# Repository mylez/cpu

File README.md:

#### Miles Smith

# 16-Bit Multiprogram Computer
- Supports kernel and user modes.
- Supports interrupts and exceptions for segmentation violations, timeouts, IO etc (via kernel routine).
- Supports user memory protection through virtual pages (64KB data / 128KB code address space per process).
- Supports preemptive multiprogramming via a hardware timer.

## Instruction Set Architecture (ISA)
##### Total: 57 instructions (57 of 128 opcodes reserved)

### Arithmetic Instructions
##### (16)
    add  rx ry rz           (rx <- ry + rz, status updated)
    sub  rx ry rz           (rx <- ry + rz, status updated)
    and  rx ry rz           (rx <- ry & rz, status updated)
    or   rx ry rz           (rx <- ry | rz, status updated)
    xor  rx ry rz           (rx <- ry ^ rz, status updated)
    sgx  rx ry              (rx <- sigex(ry), status updated)
    shl  rx ry              (rx <- shiftl(ry), status updated)
    shr  rx ry              (rx <- shiftr(ry), status updated)
                (imm values)
    add  rx im rz           (rx <- ry + rz, status updated)
    sub  rx im rz           (rx <- ry + rz, status updated)
    and  rx im rz           (rx <- ry & rz, status updated)
    or   rx im rz           (rx <- ry | rz, status updated)
    xor  rx im rz           (rx <- ry ^ rz, status updated)
    sgx  rx im              (rx <- sigex(ry), status updated)
    shl  rx im              (rx <- shiftl(ry), status updated)
    shr  rx im              (rx <- shiftr(ry), status updated)
     ...  (will vary based on alu implementation) ...

### MMIO Instructions
##### (15)
    l    rx ry rz           (vmem_data[ry + rz] <- rx) *
    li   imm                (r7 <- imm) *
    s    rx ry rz           (rx <- vmem_data[...]) *
    lb   rx ry rz           (vmem_data[...] <- rx, byte) *
    sb   rx ry rz           (rx <- vmem_data[...], byte) *
    ats  rx ry rz           (atomic test and set, vmem, byte) *
    lc   rx ry rz           (rx <- vmem_code[...])
    sc   rx ry rz           (vmem_code[...] <- rx)
    kl   rx ry rz           (kmem_data[...] <- rx)
    ks   rx ry rz           (rx <- kmem_data[...], byte)
    kats rx ry rz           (atomic test and set, kernel mem, byte)
    klb  rx ry rz           (rx <- kmem_data[...], byte)
    ksb  rx ry rz           (kmem_data[...] <- rx)
    klc  rx ry rz           (rx <- kmem_code[...])
    ksc  rx ry rz           (kmem_code[...] <- rx)
    
    * l, s, lb, sb, li, and ats are the only mmio instructions available to user programs
    (ie unprotected). all other MMIO instructions are protected instructions.

### Control Flow Instructions
##### (14)
    beq ry rz               branch if equal (pc <- $ry + rz)
    bne ry rz               branch if not equal
    bng ry rz               branch if negative
    bov ry rz               branch if overflow
    bcy ry rz               branch if carry
    b   ry rz               branch (unconditional)
              (imm values)
    beq im rz               branch if equal (r7 <- im, pc <- im + rz)
    bne im rz               branch if not equal
    bng im rz               branch if negative
    bov im rz               branch if overflow
    bcy im rz               branch if carry
    b   im rz
    cll im                  function call (r7 <- pc, pc <- imm, return via add, l, li, ...etc)
    sys im                  system call via exception (r7 <- return value)
      ... (will vary based on implementation) ...

### Kernel / Special Instructions
##### (12)
    ktime   rx              kernel load timer: timer <- rx
    kuser                   enable user mode
    kcaus   rx              kernel read cause: rx <- cause
    keret   rx              kernel read exception return addr: rx <- eret
    kaddr   rx              kernel read exception virtual address: rx <- exc_addr
    kcont   rx              kernel read context register: rx <- context
    krout   rx              kernel read isr register: rx <- isr
    kbase   rx              load page table base register: ptb <- rx
    kptes   rx ry rz        store page table entry, ptb[ry + rz] <- rx
    kptel   rx ry rz        load page table entry, rx <- ptb[ry + rz]
    statr   rx              read status register: rx <- status **
    statl   rx              load status register: status <- rx **

    ** statr and statl are unprotected. all others on the kernel / special list
    are protected instructions.

## Register Layout
### User Registers
There are 8 registers available to a user program. These are:

    r0 - A constant, hard-wired value of zero.
    r1 - General purpose register 1.
    r2 - General purpose register 2.
    r3 - General purpose register 3.
    r4 - Base pointer.
    r5 - Stack pointer.
    r6 - Program counter.
    r7 - Special register (imm. value / int. return value / return address)

### Kernel / Special Registers
There are 7 registers dedicated to kernel functions and special applications. These are:

    status -  Contains the result of the last ALU operation as NZVF used for conditional 
              branching. User-accessible.
    timer -   Preemption timer. Decremented while in user mode. Once it reaches zero,
              it signals a preemption exception. Protected.
    cause -   Contains information about which interrupt or exception the kernel is 
              servicing. Protected.
    eaddr -   Contains the bad virtual address that triggerred an exception, if 
              applicable. Protected.
    eret -    Contains the value of the PC when the exception/interrupt occurred. Used 
              in context switching. Protected.
    context - Contains the value of the r7 when the exception/interrupt occurred. Used 
              in context switching. Protected.
    isr -     Contains the hardwired address of the global kernel interrupt service routine.
    
### Memory Segmentation

Memory is split across both user/kernel domains as well as data/code domains. The
kernel segments are always addressed using physical addresses, while the user segments
are always addressed using virtual address translation via the MMU. In kernel mode,
the CPU will execute code from the kernel code segment. In user mode, it will execute
from the data segment.

In addition to virtual pages for user processes, processes running in kernel mode may
access the kernel RAM / ROM using physical addresses - ie there is only one kernel
address space. The CPU will begin to execute from this kernel address space on startup,
or when handling an exception.

A benefit of this approach is that it allows for data and code to occupy separate
address spaces. Data is byte-addressed. Code is 16 bit word-addressed (since all
instructions are alligned 2-byte boundaries). This provides a larger code memory (192KB in total).

A drawback of this approach is that kernel processes can not share memory with
user processes, and extra care is required in kernel mode to use the appropriate 
instruction the segment you wish to read to or write from.

## Logisim Schematics
#### CPU Main Circuit

#### MMIO Module

#### MMU Module

#### Control Module

#### Control State Diagram

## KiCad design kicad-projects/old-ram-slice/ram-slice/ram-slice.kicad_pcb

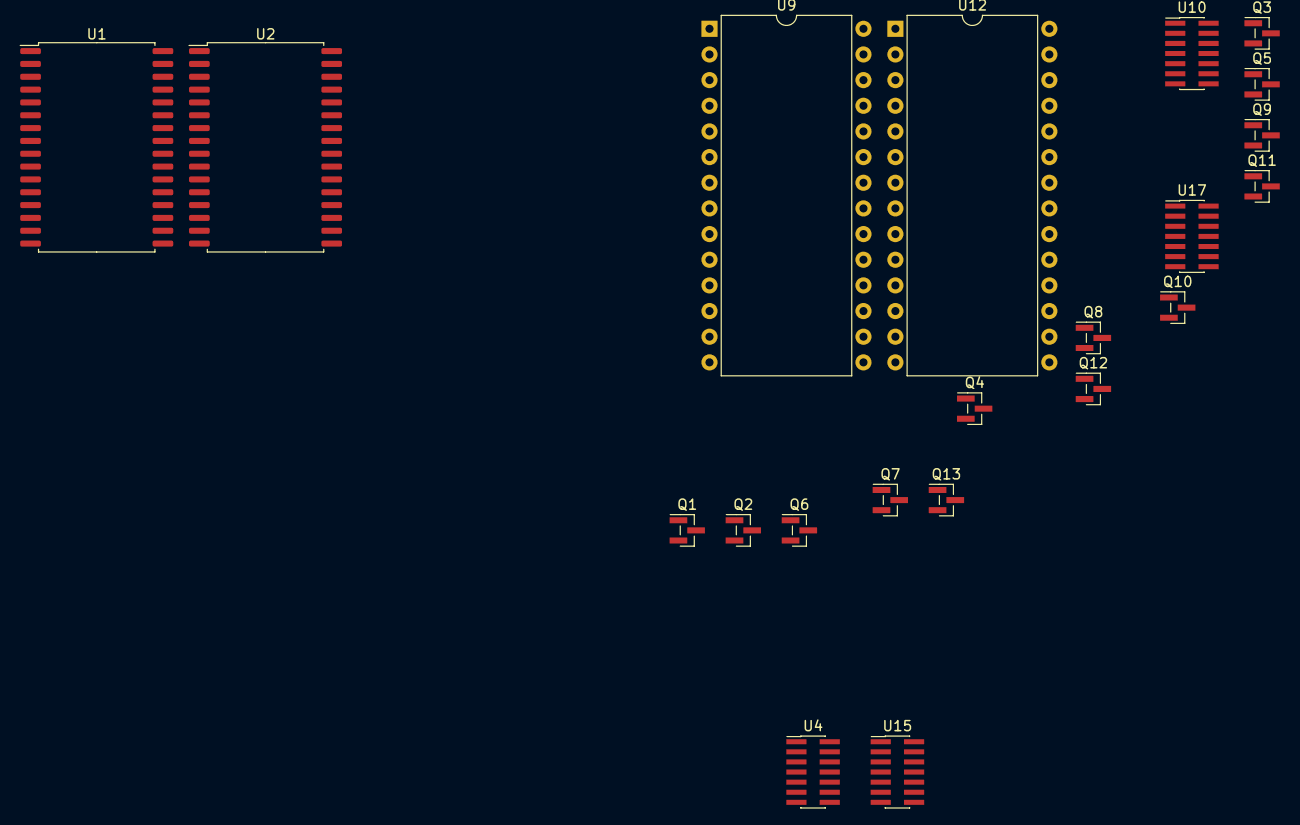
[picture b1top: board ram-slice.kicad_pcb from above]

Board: 2 copper layers, 21 parts (0 on the bottom side), 42 nets, no tracks yet.

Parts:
Q1, Q2, Q3, Q4, Q5, Q6, Q7, Q8, Q9, Q10, Q11, Q12, Q13: BS170; PinHeader_1x03_P1.00mm_Vertical_SMD_Pin1Left
U1, U2: IS61C5128AS-25QLI; SSOP-32_11.305x20.495mm_P1.27mm
U4, U10: 74LS08; PinHeader_2x07_P1.00mm_Vertical_SMD
U9, U12: 27C64; DIP-28_W15.24mm
U15: 74LS02; PinHeader_2x07_P1.00mm_Vertical_SMD
U17: 74LS32; PinHeader_2x07_P1.00mm_Vertical_SMD

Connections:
/A1: U1.12, U2.12, U9.10, U12.10
/A2: U1.11, U2.11, U9.9, U12.9
/A3: U1.10, U2.10, U9.8, U12.8
/A4: U1.9, U2.9, U9.7, U12.7
/A5: U1.8, U2.8, U9.6, U12.6
/A6: U1.7, U2.7, U9.5, U12.5
/A7: U1.6, U2.6, U9.4, U12.4
/A8: U1.5, U2.5, U9.3, U12.3
/A9: U1.27, U2.27, U9.25, U12.25
/A10: U1.26, U2.26, U9.24, U12.24
/A11: U1.23, U2.23, U9.21, U12.21
/A12: U1.25, U2.25, U9.23, U12.23
/A13: U1.4, U2.4, U9.2, U12.2
/A14: U1.28, U2.28
/A15: U1.3, U2.3
/A16: U1.31, U2.31
/A17: U1.2, U2.2
/A18: U1.1, U2.1
/A19: U1.30, U2.30
/BYTE: U4.2, U10.2
/HIGH0: U2.13, U12.11
/HIGH1: U2.14, U12.12
/HIGH2: U2.15, U12.13
/HIGH3: U2.17, U12.15
/HIGH4: U2.18, U12.16
/HIGH5: U2.19, U12.17
/HIGH6: U2.20, U12.18
/HIGH7: U2.21, U12.19
/HIGH_BYTE: U4.3, U17.4
/LOW0: U1.13, U9.11
/LOW1: U1.14, U9.12
/LOW2: U1.15, U9.13
/LOW3: U1.17, U9.15
/LOW4: U1.18, U9.16
/LOW5: U1.19, U9.17
/LOW6: U1.20, U9.18
/LOW7: U1.21, U9.19
/LOW_BYTE: U10.3, U17.1
/LOW_BYTE_ACCESSED: U17.3, U17.6
/STORE: U10.4, U10.9
/~BYTE: U17.2, U17.5
/~CLK: U10.5, U10.10

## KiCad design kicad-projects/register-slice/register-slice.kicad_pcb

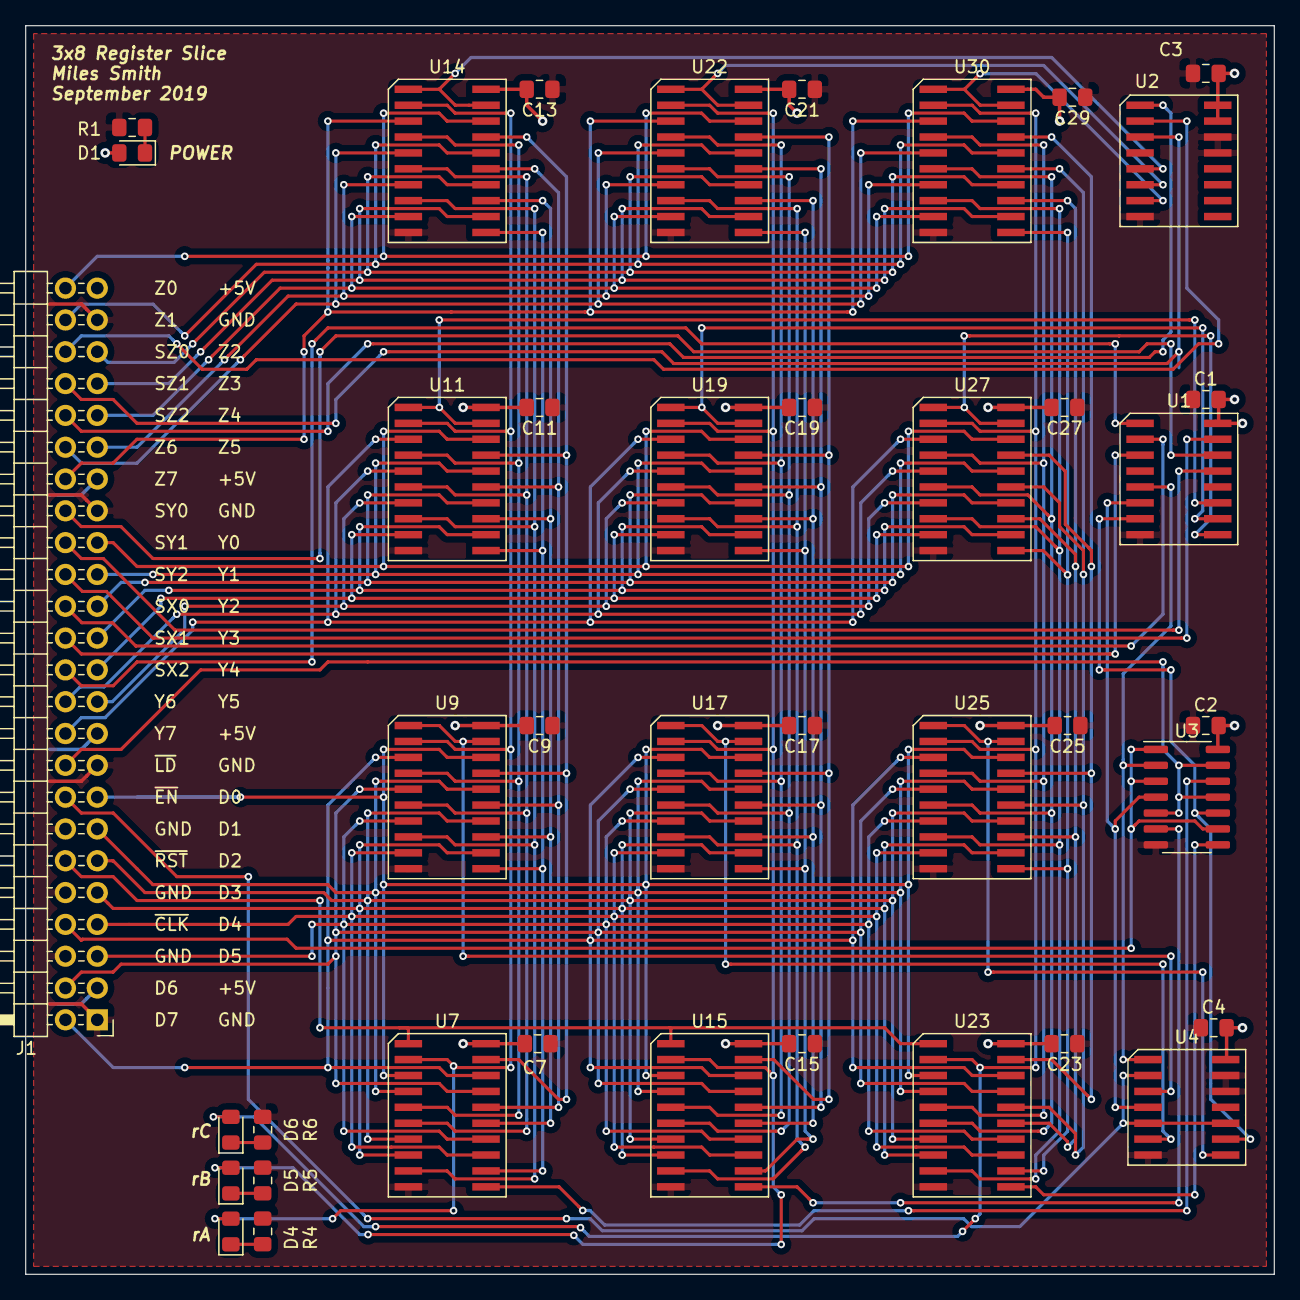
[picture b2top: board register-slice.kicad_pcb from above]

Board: 2 copper layers, 99.7 x 99.7 mm, 41 parts (0 on the bottom side), 82 nets.

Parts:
C1, C2, C3, C4, C7, C9, C11, C13, C15, C17, C19, C21, C23, C25, C27, C29: 0.1 uF; C_0805_2012Metric_Pad1.15x1.40mm_HandSolder
D1: GREEN; LED_0805_2012Metric_Pad1.15x1.40mm_HandSolder
D4, D5, D6: RED; LED_0805_2012Metric_Pad1.15x1.40mm_HandSolder
J1: Conn_02x24_Odd_Even; PinHeader_2x24_P2.54mm_Horizontal
R1, R4, R5, R6: 430; R_0805_2012Metric_Pad1.15x1.40mm_HandSolder
U1, U2: 74LS139; SOIC-16-6.2mm
U3: 74LS27; SOIC-14_3.9x8.7mm_P1.27mm
U4: 74LS32; SOIC-14-6.2mm
U7, U15, U23: 74LS273; SOIC-20-6.2mm
U9, U11, U14, U17, U19, U22, U25, U27, U30: 74LS244; SOIC-20-6.2mm

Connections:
+5V: C1.2, C2.2, C3.2, C4.2, C7.2, C9.2, C11.2, C13.2, C15.2, C17.2, C19.2, C21.2, C23.2, C25.2, C27.2, C29.2, D1.2, J1.3, J1.19, J1.35, J1.47, U1.16, U2.15, U2.16, U3.14, U4.14, U7.20, U9.20, U11.20, U14.20, U15.20, U17.20, U19.20, U22.20, U23.20, U25.20, U27.20, U30.20
/R0A: D4.2, U7.2, U9.2, U11.2, U14.2
/R0B: D5.2, U15.2, U17.2, U19.2, U22.2
/R0C: D6.2, U23.2, U25.2, U27.2, U30.2
/register_a/CP: U3.12, U7.11
/register_a/R1: U7.5, U9.4, U11.4, U14.4
/register_a/R2: U7.6, U9.6, U11.6, U14.6
/register_a/R3: U7.9, U9.8, U11.8, U14.8
/register_a/R4: U7.12, U9.11, U11.11, U14.11
/register_a/R5: U7.15, U9.13, U11.13, U14.13
/register_a/R6: U7.16, U9.15, U11.15, U14.15
/register_a/R7: U7.19, U9.17, U11.17, U14.17
/register_a/~EN_X: U4.3, U9.1, U9.19
/register_b/CP: U3.6, U15.11
/register_b/R1: U15.5, U17.4, U19.4, U22.4
/register_b/R2: U15.6, U17.6, U19.6, U22.6
/register_b/R3: U15.9, U17.8, U19.8, U22.8
/register_b/R4: U15.12, U17.11, U19.11, U22.11
/register_b/R5: U15.15, U17.13, U19.13, U22.13
/register_b/R6: U15.16, U17.15, U19.15, U22.15
/register_b/R7: U15.19, U17.17, U19.17, U22.17
/register_b/~EN_X: U4.6, U17.1, U17.19
/register_c/CP: U3.8, U23.11
/register_c/R1: U23.5, U25.4, U27.4, U30.4
/register_c/R2: U23.6, U25.6, U27.6, U30.6
/register_c/R3: U23.9, U25.8, U27.8, U30.8
/register_c/R4: U23.12, U25.11, U27.11, U30.11
/register_c/R5: U23.15, U25.13, U27.13, U30.13
/register_c/R6: U23.16, U25.15, U27.15, U30.15
/register_c/R7: U23.19, U25.17, U27.17, U30.17
/register_c/~EN_X: U4.8, U25.1, U25.19
/~EN_1_X: U1.5, U3.2, U4.1
/~EN_1_Y: U1.11, U11.1, U11.19
/~EN_1_Z: U2.5, U14.1, U14.19
/~EN_2_X: U1.6, U3.4, U4.4
/~EN_2_Y: U1.10, U19.1, U19.19
/~EN_2_Z: U2.6, U22.1, U22.19
/~EN_3_X: U1.7, U3.10, U4.9
/~EN_3_Y: U1.9, U27.1, U27.19
/~EN_3_Z: U2.7, U30.1, U30.19
D0: J1.15, U7.3, U9.18, U15.3, U17.18, U23.3, U25.18
D1: J1.13, U7.4, U9.16, U15.4, U17.16, U23.4, U25.16
D2: J1.11, U7.7, U9.14, U15.7, U17.14, U23.7, U25.14
D3: J1.9, U7.8, U9.12, U15.8, U17.12, U23.8, U25.12
D4: J1.7, U7.13, U9.9, U15.13, U17.9, U23.13, U25.9
D5: J1.5, U7.14, U9.7, U15.14, U17.7, U23.14, U25.7
D6: J1.4, U7.17, U9.5, U15.17, U17.5, U23.17, U25.5
D7: J1.2, U7.18, U9.3, U15.18, U17.3, U23.18, U25.3
GND: C1.1, C2.1, C3.1, C4.1, C7.1, C9.1, C11.1, C13.1, C15.1, C17.1, C19.1, C21.1, C23.1, C25.1, C27.1, C29.1, J1.1, J1.6, J1.10, J1.14, J1.17, J1.33, J1.45, R1.2, R4.2, R5.2, R6.2, U1.8, U2.8, U2.13, U2.14, U3.7, U4.7, U4.12, U4.13, U7.10, U9.10, U11.10, U14.10, U15.10, U17.10, U19.10, U22.10, U23.10, U25.10, U27.10, U30.10
unnamed: D1.1, R1.1
unnamed: D4.1, R4.1
unnamed: D5.1, R5.1
unnamed: D6.1, R6.1
SEL_X_0: J1.28, U1.2
SEL_X_1: J1.26, U1.3
SEL_Y_0: J1.34, U1.14
SEL_Y_1: J1.32, U1.13
SEL_Z_0: J1.44, U2.2
SEL_Z_1: J1.42, U2.3
Y0: J1.31, U11.18, U19.18, U27.18
Y1: J1.29, U11.16, U19.16, U27.16
Y2: J1.27, U11.14, U19.14, U27.14
Y3: J1.25, U11.12, U19.12, U27.12
Y4: J1.23, U11.9, U19.9, U27.9
Y5: J1.21, U11.7, U19.7, U27.7
Y6: J1.22, U11.5, U19.5, U27.5
Y7: J1.20, U11.3, U19.3, U27.3
Z0: J1.48, U14.18, U22.18, U30.18
Z1: J1.46, U14.16, U22.16, U30.16
Z2: J1.43, U14.14, U22.14, U30.14
Z3: J1.41, U14.12, U22.12, U30.12
Z4: J1.39, U14.9, U22.9, U30.9
Z5: J1.37, U14.7, U22.7, U30.7
Z6: J1.38, U14.5, U22.5, U30.5
Z7: J1.36, U14.3, U22.3, U30.3
~CLK: J1.8, U3.1, U3.3, U3.9
~EN_REG_D: J1.16, U4.2, U4.5, U4.10
~REG_LOAD: J1.18, U3.5, U3.11, U3.13
~RESET: J1.12, U7.1, U15.1, U23.1
~SEL_X_2: J1.24, U1.1
~SEL_Y_2: J1.30, U1.15
~SEL_Z_2: J1.40, U2.1

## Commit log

2020-08-03 stuff
2020-08-05 potentially working mmio interface
2020-08-11 add mmio files
2020-09-01 vmem
2021-01-01 control unit photo
2021-01-03 roughly completed
2021-01-05 cleaning main
2021-01-05 cleaning up
2021-01-05 cleaning up, taking pictures
2021-01-05 readme
2021-01-05 docs
2021-01-05 Rename isa.txt to isa.md
2021-01-05 add images
2021-01-05 control fsm pic
2021-01-05 update pic
2021-01-15 update photos and circuit
2021-03-22 add image
2021-05-20 text change
